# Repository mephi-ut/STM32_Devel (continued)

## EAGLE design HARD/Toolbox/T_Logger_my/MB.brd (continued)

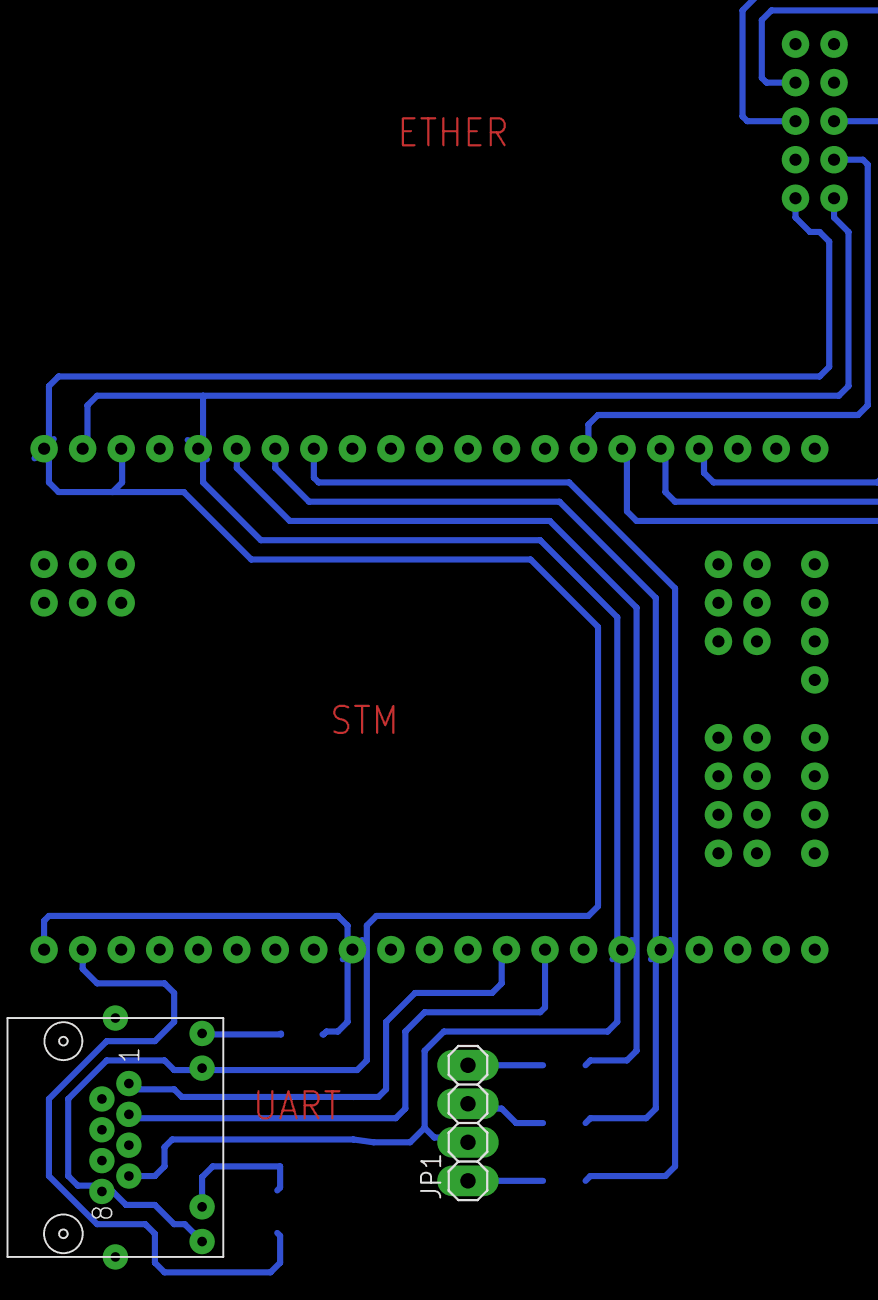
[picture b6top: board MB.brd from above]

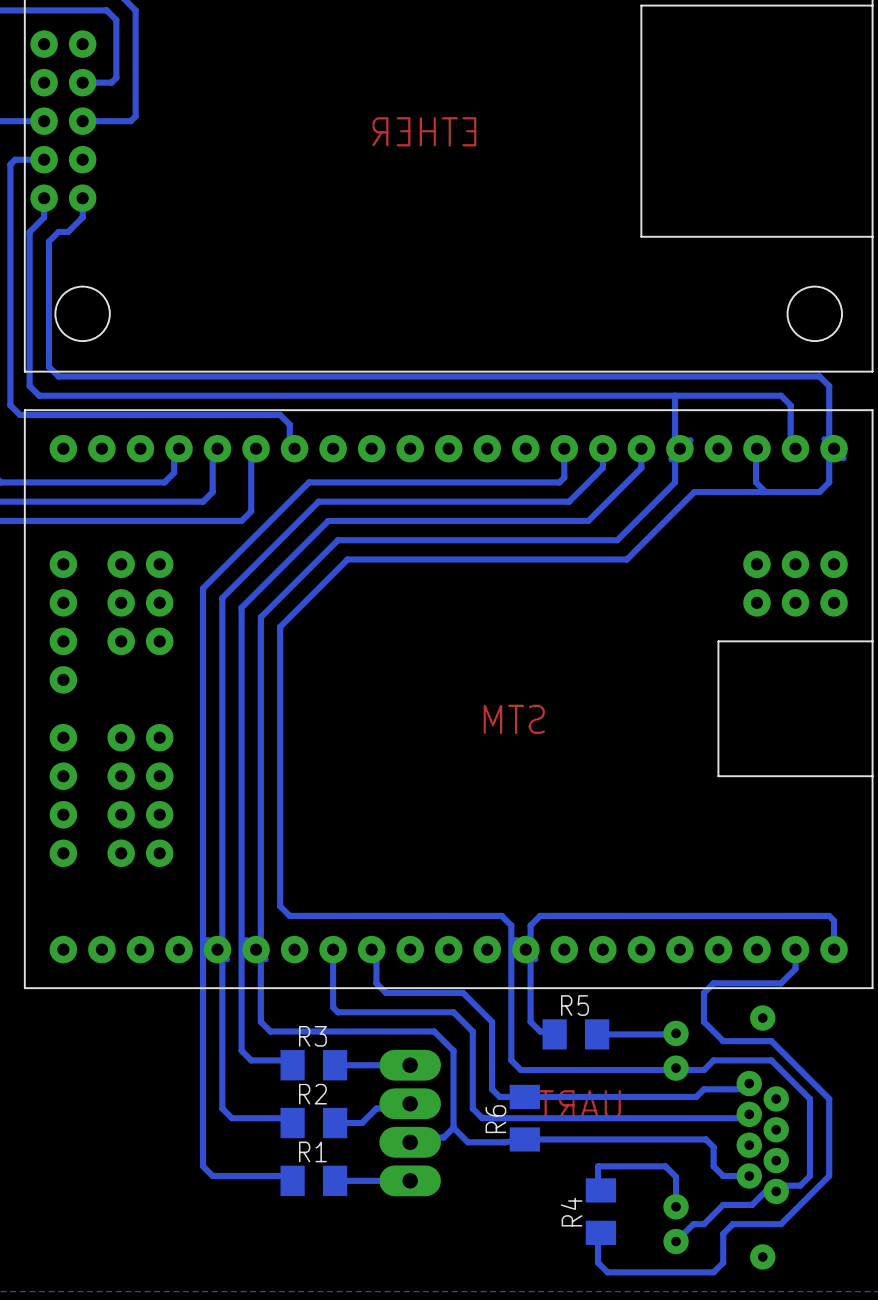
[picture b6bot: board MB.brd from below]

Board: 2 copper layers, 10 parts (8 on the bottom side), 18 nets.

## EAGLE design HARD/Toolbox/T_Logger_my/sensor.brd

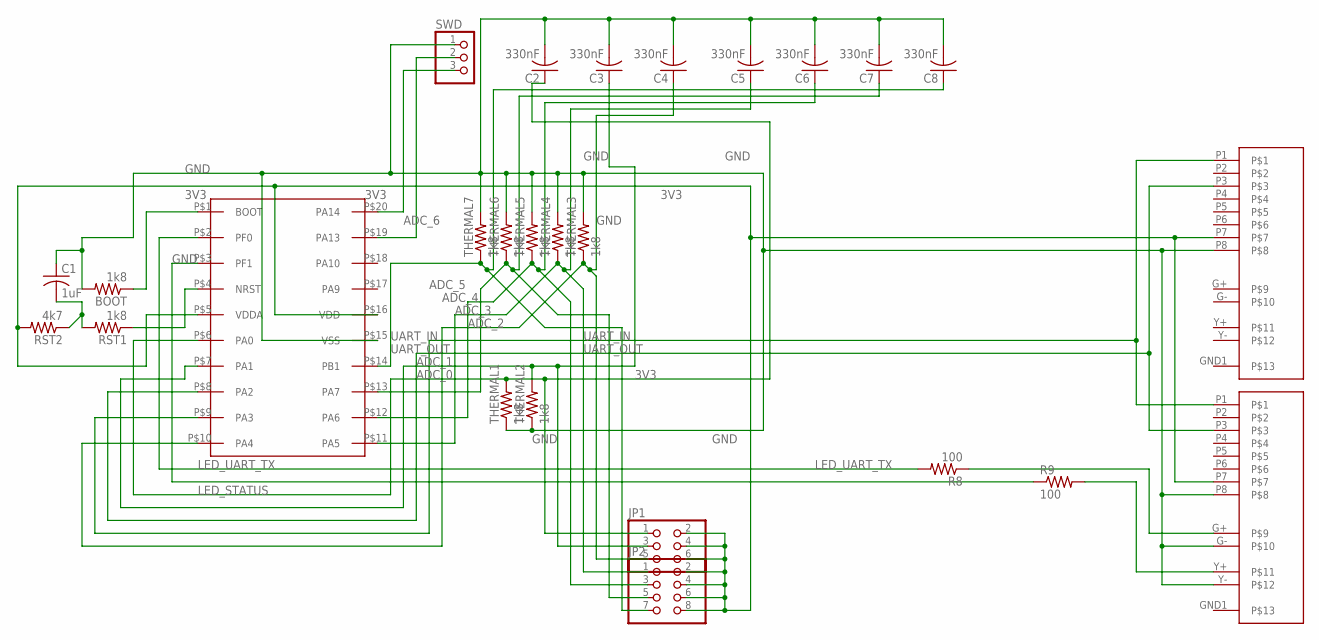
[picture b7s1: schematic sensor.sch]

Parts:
BOOT: 1k8; R1206
C1: 1uF; C0805
C2, C3, C4, C5, C6, C7, C8: 330nF; C0805
JP1: PINHD-2X3; 2X03
JP2: PINHD-2X4; 2X04
R8, R9: 100; R1206
RST1: 1k8; R1206
RST2: 4k7; R1206
SWD: PINHD-1X3; 1X03
THERMAL1, THERMAL2, THERMAL3, THERMAL4, THERMAL5, THERMAL6, THERMAL7: 1k8; R1206
U$1, U$2: RJ-45_LEDS
U$3: STM32F030; TSSOP-TO-DIP20-600

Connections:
3V3: JP1.2, JP1.4, JP1.6, JP2.2, JP2.4, JP2.6, JP2.8, RST2.2, U$1.P7, U$2.P7, U$3.P$5 (VDDA), U$3.P$16 (VDD)
ADC_0: C2.1, JP1.1, THERMAL1.2, U$3.P$6 (PA0)
ADC_1: C3.1, JP1.3, THERMAL2.2, U$3.P$7 (PA1)
ADC_2: C4.1, JP1.5, THERMAL3.1, U$3.P$10 (PA4)
ADC_3: C5.1, JP2.1, THERMAL4.1, U$3.P$11 (PA5)
ADC_4: C6.1, JP2.3, THERMAL5.1, U$3.P$12 (PA6)
ADC_5: C7.1, JP2.5, THERMAL6.1, U$3.P$13 (PA7)
ADC_6: C8.1, JP2.7, THERMAL7.1, U$3.P$14 (PB1)
GND: BOOT.2, C1.1, C2.2, C3.2, C4.2, C5.2, C6.2, C7.2, C8.2, SWD.1, THERMAL1.1, THERMAL2.1, THERMAL3.2, THERMAL4.2, THERMAL5.2, THERMAL6.2, THERMAL7.2, U$1.P8, U$2.G-, U$2.P8, U$2.Y-, U$3.P$15 (VSS)
LED_STATUS: R9.1, U$3.P$3 (PF1)
LED_UART_TX: R8.2, U$3.P$2 (PF0)
unnamed: R8.1, U$2.G+
unnamed: R9.2, U$2.Y+
unnamed: BOOT.1, U$3.P$1 (BOOT)
unnamed: RST1.1, U$3.P$4 (NRST)
unnamed: C1.2, RST1.2, RST2.1
unnamed: SWD.3, U$3.P$20 (PA14)
unnamed: SWD.2, U$3.P$19 (PA13)
P$9: U$1.G+
P$10: U$1.G-
P$11: U$1.Y+
P$12: U$1.Y-
P$13: U$1.GND1, U$2.GND1
UART_IN: U$1.P1, U$2.P1, U$3.P$9 (PA3)
UART_OUT: U$1.P3, U$2.P3, U$3.P$8 (PA2)

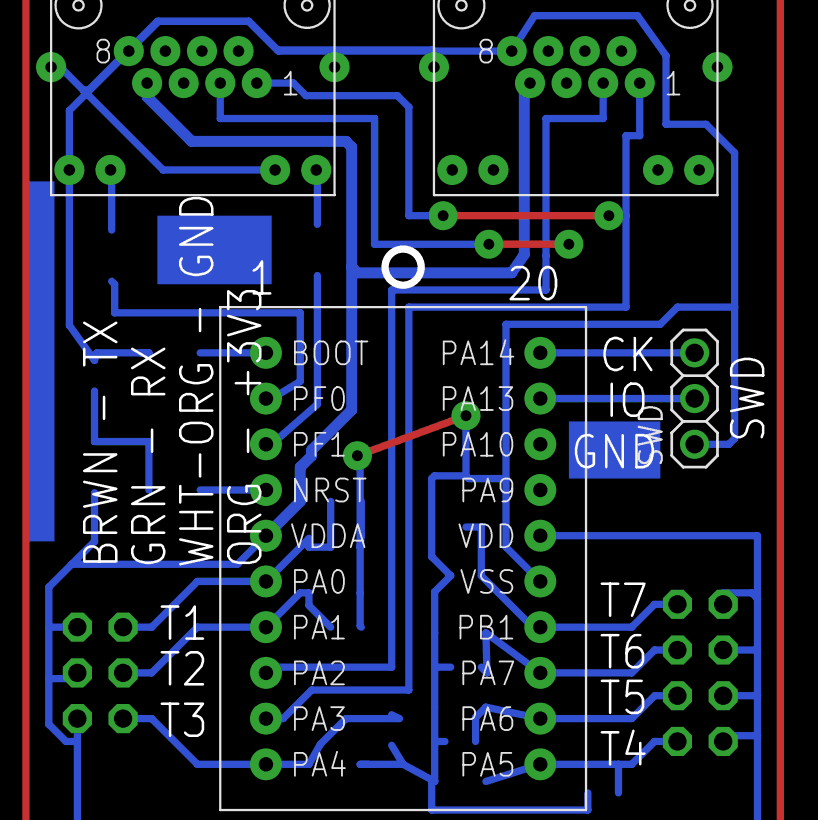
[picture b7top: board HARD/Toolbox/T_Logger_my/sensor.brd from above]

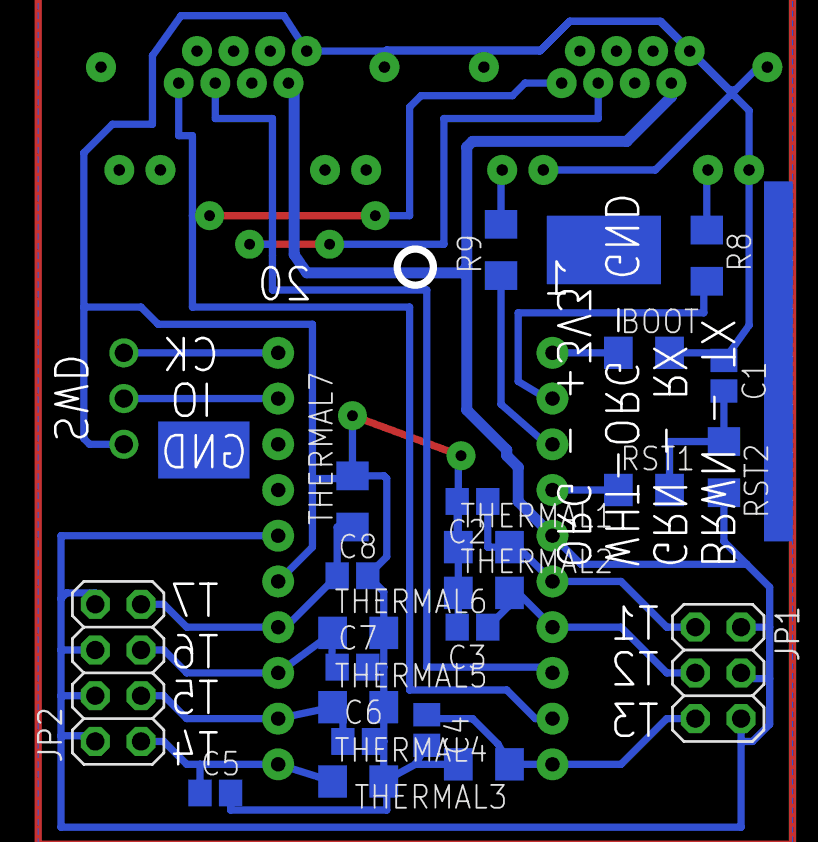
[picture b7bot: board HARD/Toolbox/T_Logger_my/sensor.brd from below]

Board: 2 copper layers, 26 parts (22 on the bottom side), 21 nets.
